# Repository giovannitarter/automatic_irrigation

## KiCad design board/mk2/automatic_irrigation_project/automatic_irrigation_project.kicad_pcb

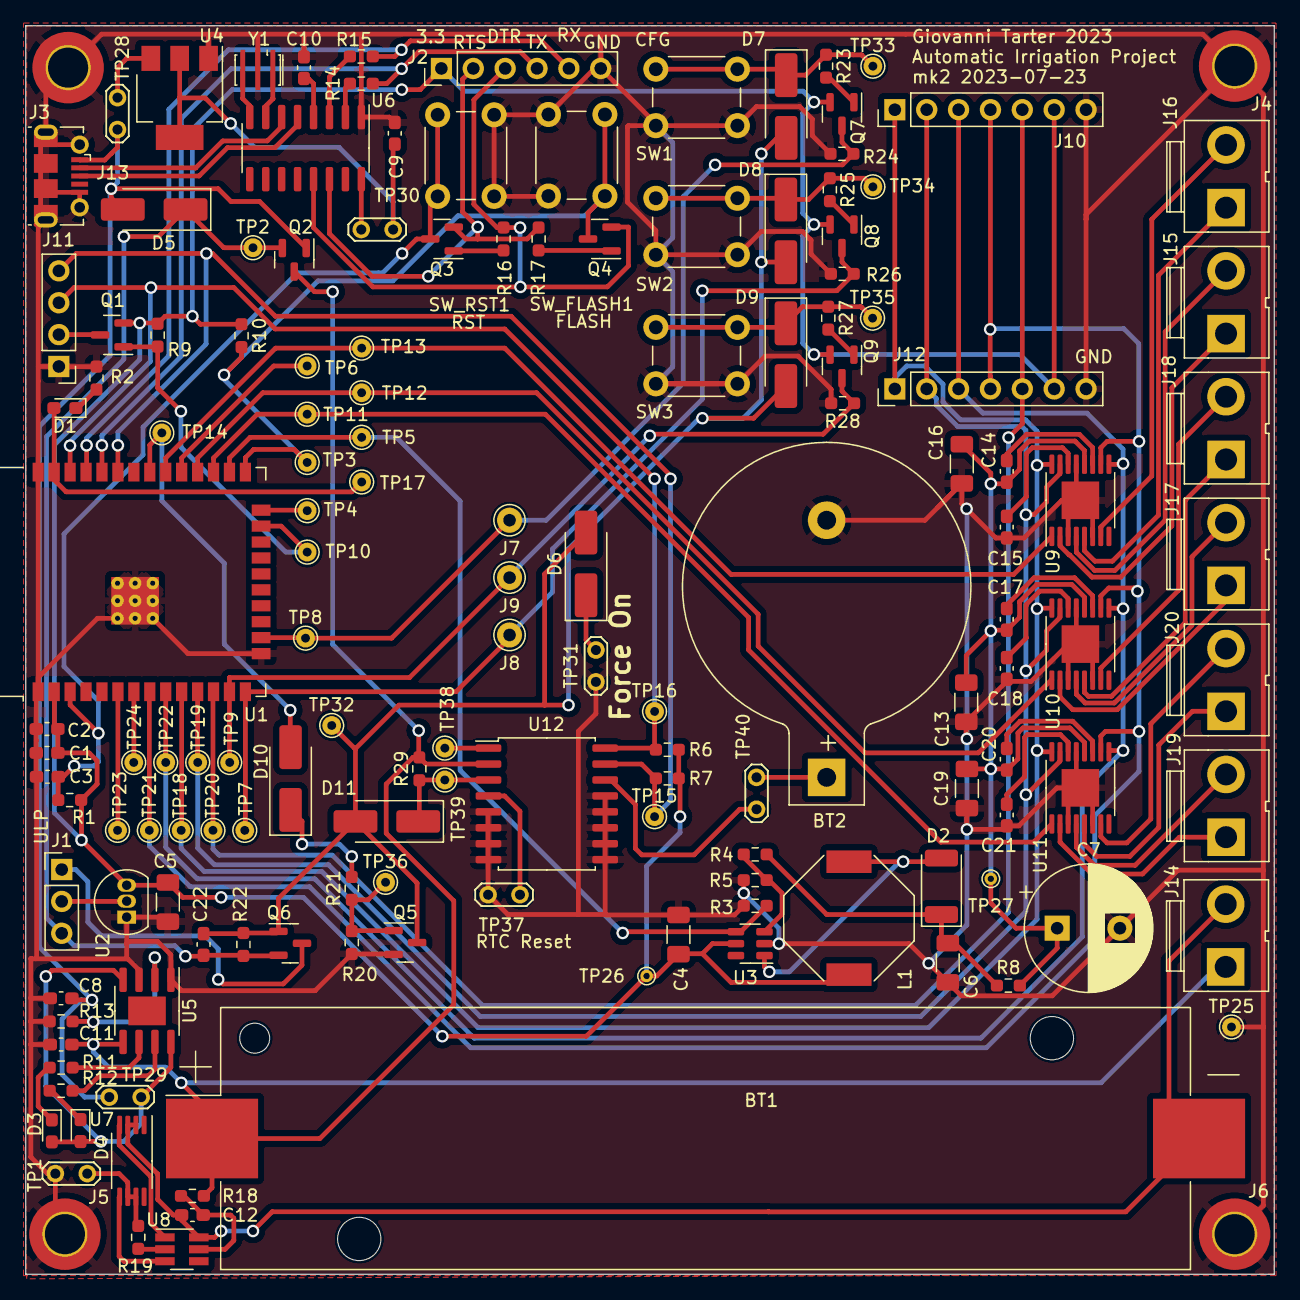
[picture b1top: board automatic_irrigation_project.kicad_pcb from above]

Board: 2 copper layers, 99.5 x 99.5 mm, 152 parts (0 on the bottom side), 97 nets.

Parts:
BT1: Battery; BatteryHolder_Keystone_1042_1x18650
BT2: Battery_Cell; BatteryHolder_Keystone_103_1x20mm
C1, C3, C9, C11: 10uF; C_0603_1608Metric_Pad1.08x0.95mm_HandSolder
C2, C8, C10, C14, C17, C20: 0.1uF; C_0603_1608Metric_Pad1.08x0.95mm_HandSolder
C4, C6: 22uF; C_1206_3216Metric_Pad1.33x1.80mm_HandSolder
C5: 100uF; C_1206_3216Metric_Pad1.33x1.80mm_HandSolder
C7: 1000uF; CP_Radial_D10.0mm_P5.00mm
C12: 100nF; C_0603_1608Metric_Pad1.08x0.95mm_HandSolder
C13, C16, C19: 10uF; C_1206_3216Metric_Pad1.33x1.80mm_HandSolder
C15, C18, C21: 2.2uF; C_0603_1608Metric_Pad1.08x0.95mm_HandSolder
C22: 10n; C_0603_1608Metric_Pad1.08x0.95mm_HandSolder
D1: LED; LED_0603_1608Metric_Pad1.05x0.95mm_HandSolder
D2: 1SS355VM; D_2010_5025Metric
D3: LED G; LED_0603_1608Metric_Pad1.05x0.95mm_HandSolder
D4: LED R; LED_0603_1608Metric_Pad1.05x0.95mm_HandSolder
D5: SS14; D_SMA_Handsoldering
D6, D7, D8, D9, D10, D11: 1N5817; D_SMA_Handsoldering
J1: Conn_01x03_Pin; PinHeader_1x03_P2.54mm_Vertical
J2: Conn_01x06_Pin; PinHeader_1x06_P2.54mm_Vertical
J3, J4, J5, J6: Conn_01x01_Pin; MountingHole_3.2mm_M3_ISO7380_Pad_TopBottom
J7, J8, J9: Conn_01x01_Pin; Pin_D1.0mm_L10.0mm
J10, J12: Conn_01x07_Pin; PinHeader_1x07_P2.54mm_Vertical
J11: Conn_01x04_Pin; PinHeader_1x04_P2.54mm_Vertical
J13: USB_B_Micro; USB_Micro-B_Molex-105017-0001
J14, J15, J16, J17, J18, J19, J20: Conn_01x02; Terminal_5mm
L1: 22uH; L_Bourns-SRU1028_10.0x10.0mm
Q1, Q2, Q6: AO3401A; SOT-23
Q3, Q4, Q5: BC817; SOT-23
Q7, Q8, Q9: BC807; SOT-23
R1, R3, R6, R7, R10, R20, R22, R29: 100K; R_0603_1608Metric_Pad0.98x0.95mm_HandSolder
R2: 330; R_0603_1608Metric_Pad0.98x0.95mm_HandSolder
R4: 180K; R_0603_1608Metric_Pad0.98x0.95mm_HandSolder
R5, R9, R16, R17, R21, R23, R24, R25, R26, R27, R28: 10K; R_0603_1608Metric_Pad0.98x0.95mm_HandSolder
R8, R18: 100 Ohm; R_0603_1608Metric_Pad0.98x0.95mm_HandSolder
R11, R12, R13: 1K; R_0603_1608Metric_Pad0.98x0.95mm_HandSolder
R14, R15: 220; R_0603_1608Metric_Pad0.98x0.95mm_HandSolder
R19: 1k; R_0603_1608Metric_Pad0.98x0.95mm_HandSolder
SW1, SW2, SW3: SW_Push; SW_PUSH_6mm_H4.3mm
SW_FLASH1: SW_Push; SW_PUSH_6mm_H4.3mm
SW_RST1: SW_Push; SW_PUSH_6mm_H4.3mm
TP1, TP28, TP29, TP30, TP31: TestPoint_2Pole; TestPoint_2Pads_Pitch2.54mm_Drill0.8mm
TP2, TP3, TP4, TP5, TP6, TP7, TP8, TP9, TP10, TP11, TP12, TP13, TP14, TP15, TP16, TP17, TP18, TP19, TP20, TP21, TP22, TP23, TP24, TP25, TP32, TP33, TP34, TP35, TP36, TP38, TP39: TestPoint_Probe; TestPoint_THTPad_D1.5mm_Drill0.7mm
TP26, TP27: TestPoint; TestPoint_THTPad_D1.0mm_Drill0.5mm
TP37: RTC Reset; TestPoint_2Pads_Pitch2.54mm_Drill0.8mm
TP40: Bat Exclusion; TestPoint_2Pads_Pitch2.54mm_Drill0.8mm
U1: ESP32-WROOM-32D
U2: HT7333; TO-92L_Inline
U3: MT3608; SOT-23-6
U4: AMS1117-3.3; SOT-223-3_TabPin2
U5: TP4056; SOIC-8-1EP_3.9x4.9mm_P1.27mm_EP2.29x3mm
U6: CH340G; SOIC-16_3.9x9.9mm_P1.27mm
U7: FS8205A; TSSOP-8_4.4x3mm_P0.65mm
U8: DW01; SOT-23-6_Handsoldering
U9, U10, U11: DRV8833PW; HTSSOP-16-1EP_4.4x5mm_P0.65mm_EP3x3mm
U12: DS3231M; SOIC-16W_7.5x10.3mm_P1.27mm
Y1: Resonator; Resonator_SMD_Murata_CSTxExxV-3Pin_3.0x1.1mm_HandSoldering

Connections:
+3.3V: C1.1, C2.1, C4.1, C5.1, J2.1, J10.6, J12.6, L1.1, Q1.2 (S), Q7.2 (E), Q8.2 (E), Q9.2 (E), R1.2, R6.1, R7.1, R9.2, R10.1, TP26.1, U1.2 (VDD), U2.3 (OUT), U3.5 (IN)
+10V: C7.1, C13.1, C14.1, C16.1, C17.1, C19.1, C20.1, R8.2, TP27.1, U9.12 (VM), U10.12 (VM), U11.12 (VM)
+BATT: BT1.1 (+), C11.1, J14.1, Q2.3 (D), R18.2, R29.2, U5.5 (BAT), U12.2 (VCC)
/AIN1: J10.1, J12.1, TP18.1, U1.10 (IO25), U9.16 (AIN1), U10.16 (AIN1), U11.16 (AIN1)
/AIN2: J10.2, J12.2, TP19.1, U1.11 (IO26), U9.15 (AIN2), U10.15 (AIN2), U11.15 (AIN2)
/AUX: J10.5, J12.5, TP20.1, U1.12 (IO27)
/BIN1: J10.3, J12.3, TP22.1, U1.9 (IO33), U9.9 (BIN1), U10.9 (BIN1), U11.9 (BIN1)
/BIN2: J10.4, J12.4, TP21.1, U1.8 (IO32), U9.10 (BIN2), U10.10 (BIN2), U11.10 (BIN2)
/DISP_VCC: Q1.1 (G), R9.1, TP10.1, U1.23 (IO15)
/H_BRIDGE_EN1: TP13.1, U1.30 (IO18), U9.1 (nSLEEP)
/H_BRIDGE_EN2: TP12.1, U1.28 (IO17), U10.1 (nSLEEP)
/H_BRIDGE_EN3: TP11.1, U1.27 (IO16), U11.1 (nSLEEP)
/LATCH: D10.2 (A), TP14.1, U1.31 (IO19)
/RTC_INT: D11.1 (K), R29.1, TP39.1, U12.3 (~INT/SQW)
/SCL: J11.3, R6.2, TP16.1, U1.36 (IO22), U12.16 (SCL)
/SDA: J11.4, R7.2, TP15.1, U1.33 (IO21), U12.15 (SDA)
/STEP_UP_EN: R3.1, TP5.1, U1.26 (IO4), U3.4 (EN)
/SW1: J7.1, Q7.3 (C), R24.1, TP8.1, U1.16 (IO13)
/SW2: J8.1, Q8.3 (C), R26.1, TP7.1, U1.14 (IO12)
/SW3: J9.1, Q9.3 (C), R28.1, TP9.1, U1.13 (IO14)
/battery/BAT-: R19.2, TP1.2, U7.6 (S2), U7.7 (S2)
/power_latch/Vin: C22.1, D5.1 (K), J1.3, Q2.2 (S), Q6.2 (S), R22.2, TP2.1
/power_latch/Vout: J1.1, Q6.3 (D)
DTR: J2.3, Q4.2 (E), R16.1, U6.13 (~DTR)
EN: C3.1, Q3.3 (C), R1.1, SW_RST1.2, U1.3 (EN)
GND: BT2.2 (-), C1.2, C2.2, C3.2, C4.2, C5.2, C6.2, C7.2, C8.2, C9.2, C10.2, C11.2, C13.2, C15.2, C16.2, C18.2, C19.2, C21.2, J2.6, J3.1, J4.1, J5.1, J6.1, J10.7, J11.1, J12.7, J13.5 (GND), J13.6 (Shield), Q5.2 (E), R2.2, R3.2, R5.2, R13.1, R20.2, R24.2, R26.2, R28.2, SW1.1, SW2.1, SW3.1, SW_FLASH1.1, SW_RST1.1, TP1.1, TP25.1, TP31.1, TP37.1, U1.1 (GND), U1.15 (GND), U1.38 (GND), U1.39 (GND), U2.1 (GND), U3.2 (GND), U4.1 (GND), U5.1 (TEMP), U5.3 (GND), U6.1 (GND), U9.3 (AISEN), U9.6 (BISEN), U9.13 (GND), U9.17 (ThermalPad), U10.3 (AISEN), U10.6 (BISEN), U10.13 (GND), U10.17 (ThermalPad), U11.3 (AISEN), U11.6 (BISEN), U11.13 (GND), U11.17 (ThermalPad), U12.5 (GND), U12.6 (GND), U12.7 (GND), U12.8 (GND), U12.9 (GND), U12.10 (GND), U12.11 (GND), U12.12 (GND), U12.13 (GND), Y1.2
IO0: Q4.3 (C), R10.2, SW_FLASH1.2, TP3.1, U1.25 (IO0)
unnamed: BT1.2 (-), C12.2, J14.2, U7.2 (S1), U7.3 (S1), U8.6 (GND)
unnamed: BT2.1 (+), TP40.1
unnamed: D1.2 (A), TP17.1, U1.37 (IO23)
unnamed: D1.1 (K), R2.1
unnamed: D2.2 (A), L1.2, U3.1 (SW)
unnamed: C6.1, D2.1 (K), R4.1, R8.1
unnamed: D3.2 (A), D4.2 (A), TP29.1, U5.4 (VCC), U5.8 (CE)
unnamed: D3.1 (K), R11.2
unnamed: D4.1 (K), R12.2
unnamed: D6.1 (K), TP31.2
unnamed: D7.1 (K), R23.1, SW1.2, TP33.1
unnamed: D8.1 (K), R25.1, SW2.2, TP34.1
unnamed: D9.1 (K), R27.1, SW3.2, TP35.1
unnamed: D10.1 (K), R21.2
unnamed: C22.2, D6.2 (A), D7.2 (A), D8.2 (A), D9.2 (A), D11.2 (A), Q5.3 (C), Q6.1 (G), R22.1, TP32.1
unnamed: J1.2, U2.2 (IN)
unnamed: J11.2, Q1.3 (D)
unnamed: J13.3 (D+), U6.5 (UD+)
unnamed: J13.2 (D-), U6.6 (UD-)
unnamed: J15.1, U9.2 (AOUT1)
unnamed: J15.2, U9.4 (AOUT2)
unnamed: J16.1, U9.5 (BOUT2)
unnamed: J16.2, U9.7 (BOUT1)
unnamed: J17.1, U10.2 (AOUT1)
unnamed: J17.2, U10.4 (AOUT2)
unnamed: J18.1, U10.5 (BOUT2)
unnamed: J18.2, U10.7 (BOUT1)
unnamed: J19.1, U11.2 (AOUT1)
unnamed: J19.2, U11.4 (AOUT2)
unnamed: J20.1, U11.5 (BOUT2)
unnamed: J20.2, U11.7 (BOUT1)
unnamed: Q3.1 (B), R16.2
unnamed: Q4.1 (B), R17.2
unnamed: Q5.1 (B), R20.1, R21.1, TP36.1
unnamed: Q7.1 (B), R23.2
unnamed: Q8.1 (B), R25.2
unnamed: Q9.1 (B), R27.2
unnamed: TP4.1, U1.24 (IO2)
unnamed: TP6.1, U1.29 (IO5)
unnamed: TP23.1, U1.6 (IO34)
unnamed: TP24.1, U1.7 (IO35)
unnamed: R4.2, R5.1, U3.3 (FB)
unnamed: TP28.2, U4.3 (VI)
unnamed: C9.1, TP30.2, U4.2 (VO)
unnamed: R13.2, U5.2 (PROG)
unnamed: R12.1, U5.7 (~CHRG)
unnamed: R11.1, U5.6 (~STDBY)
unnamed: R15.1, U6.3 (RXD)
unnamed: R14.1, U6.2 (TXD)
unnamed: C10.1, U6.4 (V3)
unnamed: TP30.1, U6.16 (VCC)
unnamed: U6.7 (XI), Y1.1
unnamed: U6.8 (XO), Y1.3
unnamed: U7.4 (G1), U8.1 (OD)
unnamed: U7.5 (G2), U8.3 (OC)
unnamed: R19.1, U8.2 (CS)
unnamed: C12.1, R18.1, U8.5 (VCC)
unnamed: C14.2, U9.11 (VCP)
unnamed: C15.1, U9.14 (VINT)
unnamed: C17.2, U10.11 (VCP)
unnamed: C18.1, U10.14 (VINT)
unnamed: C20.2, U11.11 (VCP)
unnamed: C21.1, U11.14 (VINT)
unnamed: TP38.1, U12.1 (32KHZ)
unnamed: TP40.2, U12.14 (VBAT)
unnamed: TP37.2, U12.4 (~RST)
RTS: J2.2, Q3.2 (E), R17.1, U6.14 (~RTS)
RX: J2.5, R15.2, U1.35 (TXD0/IO1)
TX: J2.4, R14.2, U1.34 (RXD0/IO3)
VUSB: C8.1, D5.2 (A), J13.1 (VBUS), Q2.1 (G), TP28.1, TP29.2

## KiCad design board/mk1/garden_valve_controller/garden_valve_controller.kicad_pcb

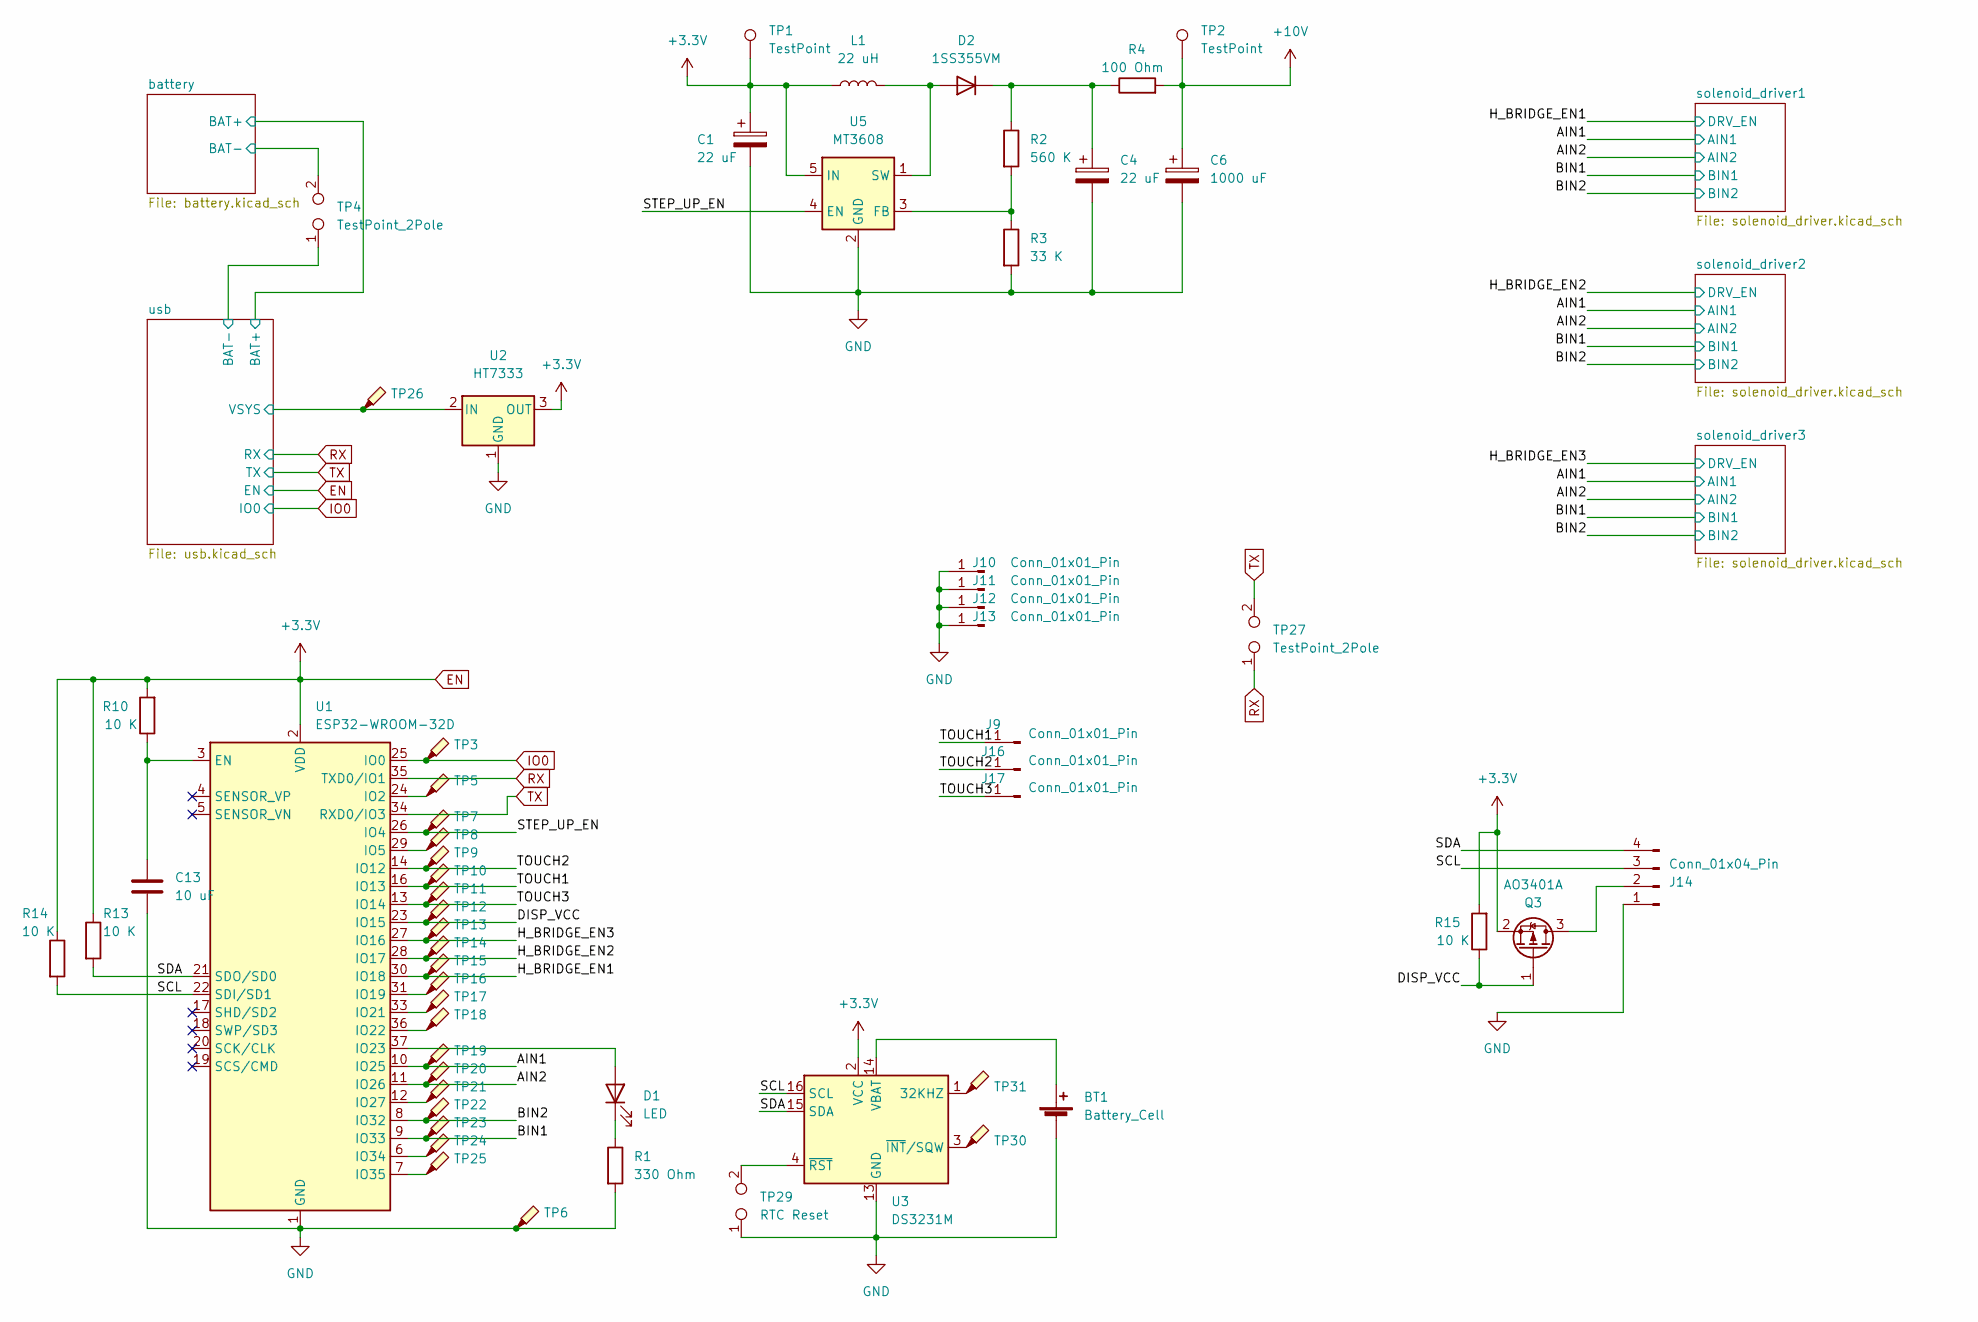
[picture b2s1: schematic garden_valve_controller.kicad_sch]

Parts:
BT1: Battery_Cell; BatteryHolder_Keystone_103_1x20mm
C1, C4: 22 uF; C_1206_3216Metric_Pad1.33x1.80mm_HandSolder
C6: 1000 uF; CP_Radial_D10.0mm_P5.00mm
C13: 10 uF; C_0603_1608Metric_Pad1.08x0.95mm_HandSolder
D1: LED; LED_D3.0mm_Clear
D2: 1SS355VM; D_2010_5025Metric
J9, J16, J17: Conn_01x01_Pin; Pin_D1.0mm_L10.0mm
J10, J11, J12, J13: Conn_01x01_Pin; MountingHole_3.2mm_M3_ISO7380_Pad_TopBottom
J14: Conn_01x04_Pin; PinHeader_1x04_P2.54mm_Vertical
L1: 22 uH; L_Bourns-SRU1028_10.0x10.0mm
Q3: AO3401A; SOT-23
R1: 330 Ohm; R_0603_1608Metric_Pad0.98x0.95mm_HandSolder
R2: 560 K; R_0603_1608Metric_Pad0.98x0.95mm_HandSolder
R3: 33 K; R_0603_1608Metric_Pad0.98x0.95mm_HandSolder
R4: 100 Ohm; R_0603_1608Metric_Pad0.98x0.95mm_HandSolder
R10, R13, R14, R15: 10 K; R_0603_1608Metric_Pad0.98x0.95mm_HandSolder
TP1, TP2: TestPoint; TestPoint_THTPad_D1.0mm_Drill0.5mm
TP3, TP5, TP6, TP7, TP8, TP9, TP10, TP11, TP12, TP13, TP14, TP15, TP16, TP17, TP18, TP19, TP20, TP21, TP22, TP23, TP24, TP25, TP26, TP30, TP31: TestPoint_Probe; TestPoint_THTPad_D1.0mm_Drill0.5mm
TP4, TP27: TestPoint_2Pole; TestPoint_2Pads_Pitch2.54mm_Drill0.8mm
TP29: RTC Reset; TestPoint_2Pads_Pitch2.54mm_Drill0.8mm
U1: ESP32-WROOM-32D
U2: HT7333; TO-92L_Inline
U3: DS3231M; SOIC-16W_7.5x10.3mm_P1.27mm
U5: MT3608; SOT-23-6

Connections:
+10V: C6.1, R4.2, TP2.1; also elsewhere on the board
/AIN1: TP19.1, U1.10 (IO25); also elsewhere on the board
/AIN2: TP20.1, U1.11 (IO26); also elsewhere on the board
/BIN1: TP23.1, U1.9 (IO33); also elsewhere on the board
/BIN2: TP22.1, U1.8 (IO32); also elsewhere on the board
/H_BRIDGE_EN1: TP15.1, U1.30 (IO18); also elsewhere on the board
/H_BRIDGE_EN2: TP14.1, U1.28 (IO17); also elsewhere on the board
/H_BRIDGE_EN3: TP13.1, U1.27 (IO16); also elsewhere on the board
/SCL: J14.3, R14.2, U1.22 (SDI/SD1), U3.16 (SCL)
/SDA: J14.4, R13.2, U1.21 (SDO/SD0), U3.15 (SDA)
/STEP_UP_EN: TP7.1, U1.26 (IO4), U5.4 (EN)
/TOUCH1: J9.1, TP10.1, U1.16 (IO13)
/TOUCH2: J16.1, TP9.1, U1.14 (IO12)
/TOUCH3: J17.1, TP11.1, U1.13 (IO14)
/battery/BAT-: TP4.2; also elsewhere on the board
GND: BT1.2 (-), C1.2, C4.2, C6.2, C13.2, J10.1, J11.1, J12.1, J13.1, J14.1, R1.2, R3.2, TP4.1, TP6.1, TP29.1, U1.1 (GND), U1.15 (GND), U1.38 (GND), U1.39 (GND), U2.1 (GND), U3.5 (GND), U3.6 (GND), U3.7 (GND), U3.8 (GND), U3.9 (GND), U3.10 (GND), U3.11 (GND), U3.12 (GND), U3.13 (GND), U5.2 (GND); also elsewhere on the board
IO0: TP3.1, U1.25 (IO0); also elsewhere on the board
unnamed: BT1.1 (+), U3.14 (VBAT)
unnamed: D1.2 (A), U1.37 (IO23)
unnamed: D1.1 (K), R1.1
unnamed: D2.2 (A), L1.2, U5.1 (SW)
unnamed: C4.1, D2.1 (K), R2.1, R4.1
unnamed: C13.1, R10.1, U1.3 (EN)
unnamed: TP5.1, U1.24 (IO2)
unnamed: TP8.1, U1.29 (IO5)
unnamed: TP16.1, U1.31 (IO19)
unnamed: TP17.1, U1.33 (IO21)
unnamed: TP18.1, U1.36 (IO22)
unnamed: TP21.1, U1.12 (IO27)
unnamed: TP24.1, U1.6 (IO34)
unnamed: TP25.1, U1.7 (IO35)
unnamed: TP31.1, U3.1 (32KHZ)
unnamed: TP30.1, U3.3 (~INT/SQW)
unnamed: TP29.2, U3.4 (~RST)
unnamed: R2.2, R3.1, U5.3 (FB)
RX: TP27.1, U1.35 (TXD0/IO1); also elsewhere on the board
TX: TP27.2, U1.34 (RXD0/IO3); also elsewhere on the board

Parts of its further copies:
Q4: AO3401A; SOT-23

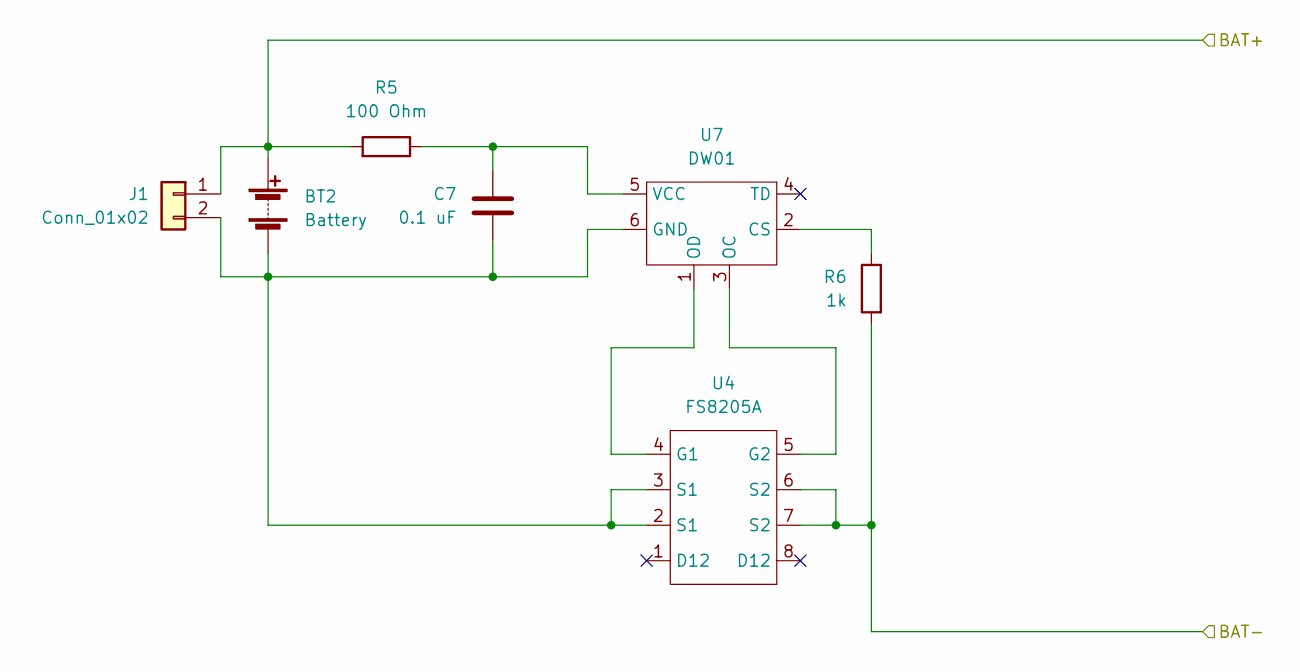
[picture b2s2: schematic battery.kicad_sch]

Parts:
BT2: Battery; BatteryHolder_MPD_BH-18650-PC2
C7: 0.1 uF; C_0603_1608Metric_Pad1.08x0.95mm_HandSolder
J1: Conn_01x02; Terminal_5mm
R5: 100 Ohm; R_0603_1608Metric_Pad0.98x0.95mm_HandSolder
R6: 1k; R_0603_1608Metric_Pad0.98x0.95mm_HandSolder
U4: FS8205A; TSSOP-8_4.4x3mm_P0.65mm
U7: DW01; SOT-23-6_Handsoldering

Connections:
/battery/BAT-: R6.2, U4.6 (S2), U4.7 (S2); also elsewhere on the board
unnamed: BT2.2 (-), C7.2, J1.2, U4.2 (S1), U4.3 (S1), U7.6 (GND)
unnamed: U4.4 (G1), U7.1 (OD)
unnamed: U4.5 (G2), U7.3 (OC)
unnamed: R6.1, U7.2 (CS)
unnamed: C7.1, R5.1, U7.5 (VCC)

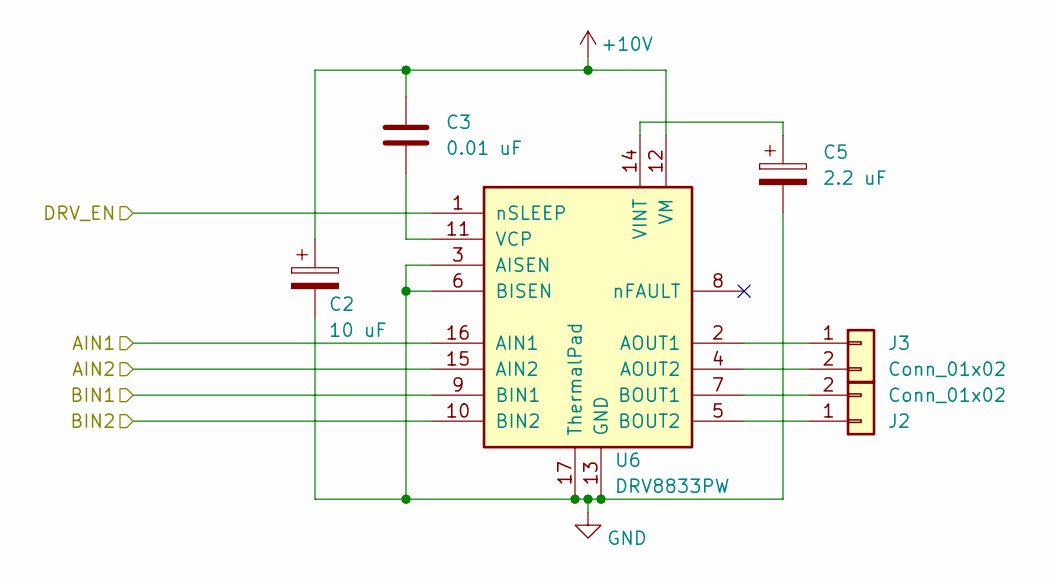
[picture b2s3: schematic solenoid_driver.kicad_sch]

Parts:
C2: 10 uF; C_1206_3216Metric_Pad1.33x1.80mm_HandSolder
C3: 0.01 uF; C_0603_1608Metric_Pad1.08x0.95mm_HandSolder
C5: 2.2 uF; C_0603_1608Metric_Pad1.08x0.95mm_HandSolder
J2, J3: Conn_01x02; Terminal_5mm
U6: DRV8833PW; HTSSOP-16-1EP_4.4x5mm_P0.65mm_EP3x3mm

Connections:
+10V: C2.1, C3.1, U6.12 (VM); also elsewhere on the board
/AIN1: U6.16 (AIN1); also elsewhere on the board
/AIN2: U6.15 (AIN2); also elsewhere on the board
/BIN1: U6.9 (BIN1); also elsewhere on the board
/BIN2: U6.10 (BIN2); also elsewhere on the board
/H_BRIDGE_EN1: U6.1 (nSLEEP); also elsewhere on the board
GND: C2.2, C5.2, U6.3 (AISEN), U6.6 (BISEN), U6.13 (GND), U6.17 (ThermalPad); also elsewhere on the board
unnamed: J2.1, U6.5 (BOUT2)
unnamed: J2.2, U6.7 (BOUT1)
unnamed: J3.1, U6.2 (AOUT1)
unnamed: J3.2, U6.4 (AOUT2)
unnamed: C3.2, U6.11 (VCP)
unnamed: C5.1, U6.14 (VINT)

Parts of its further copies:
C9, C16: 10 uF; C_1206_3216Metric_Pad1.33x1.80mm_HandSolder
C10, C17: 0.01 uF; C_0603_1608Metric_Pad1.08x0.95mm_HandSolder
C15, C18: 2.2 uF; C_0603_1608Metric_Pad1.08x0.95mm_HandSolder
J5, J6, J7, J8: Conn_01x02; Terminal_5mm
U11, U12: DRV8833PW; HTSSOP-16-1EP_4.4x5mm_P0.65mm_EP3x3mm

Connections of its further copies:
+10V: C9.1, C10.1, C16.1, C17.1, U11.12 (VM), U12.12 (VM); also elsewhere on the board
/AIN1: U11.16 (AIN1), U12.16 (AIN1); also elsewhere on the board
/AIN2: U11.15 (AIN2), U12.15 (AIN2); also elsewhere on the board
/BIN1: U11.9 (BIN1), U12.9 (BIN1); also elsewhere on the board
/BIN2: U11.10 (BIN2), U12.10 (BIN2); also elsewhere on the board
/H_BRIDGE_EN2: U11.1 (nSLEEP); also elsewhere on the board
/H_BRIDGE_EN3: U12.1 (nSLEEP); also elsewhere on the board
GND: C9.2, C15.2, C16.2, C18.2, U11.3 (AISEN), U11.6 (BISEN), U11.13 (GND), U11.17 (ThermalPad), U12.3 (AISEN), U12.6 (BISEN), U12.13 (GND), U12.17 (ThermalPad); also elsewhere on the board
unnamed: J5.1, U11.5 (BOUT2)
unnamed: J5.2, U11.7 (BOUT1)
unnamed: J6.1, U11.2 (AOUT1)
unnamed: J6.2, U11.4 (AOUT2)
unnamed: J7.1, U12.5 (BOUT2)
unnamed: J7.2, U12.7 (BOUT1)
unnamed: J8.1, U12.2 (AOUT1)
unnamed: J8.2, U12.4 (AOUT2)
unnamed: C10.2, U11.11 (VCP)
unnamed: C15.1, U11.14 (VINT)
unnamed: C17.2, U12.11 (VCP)
unnamed: C18.1, U12.14 (VINT)

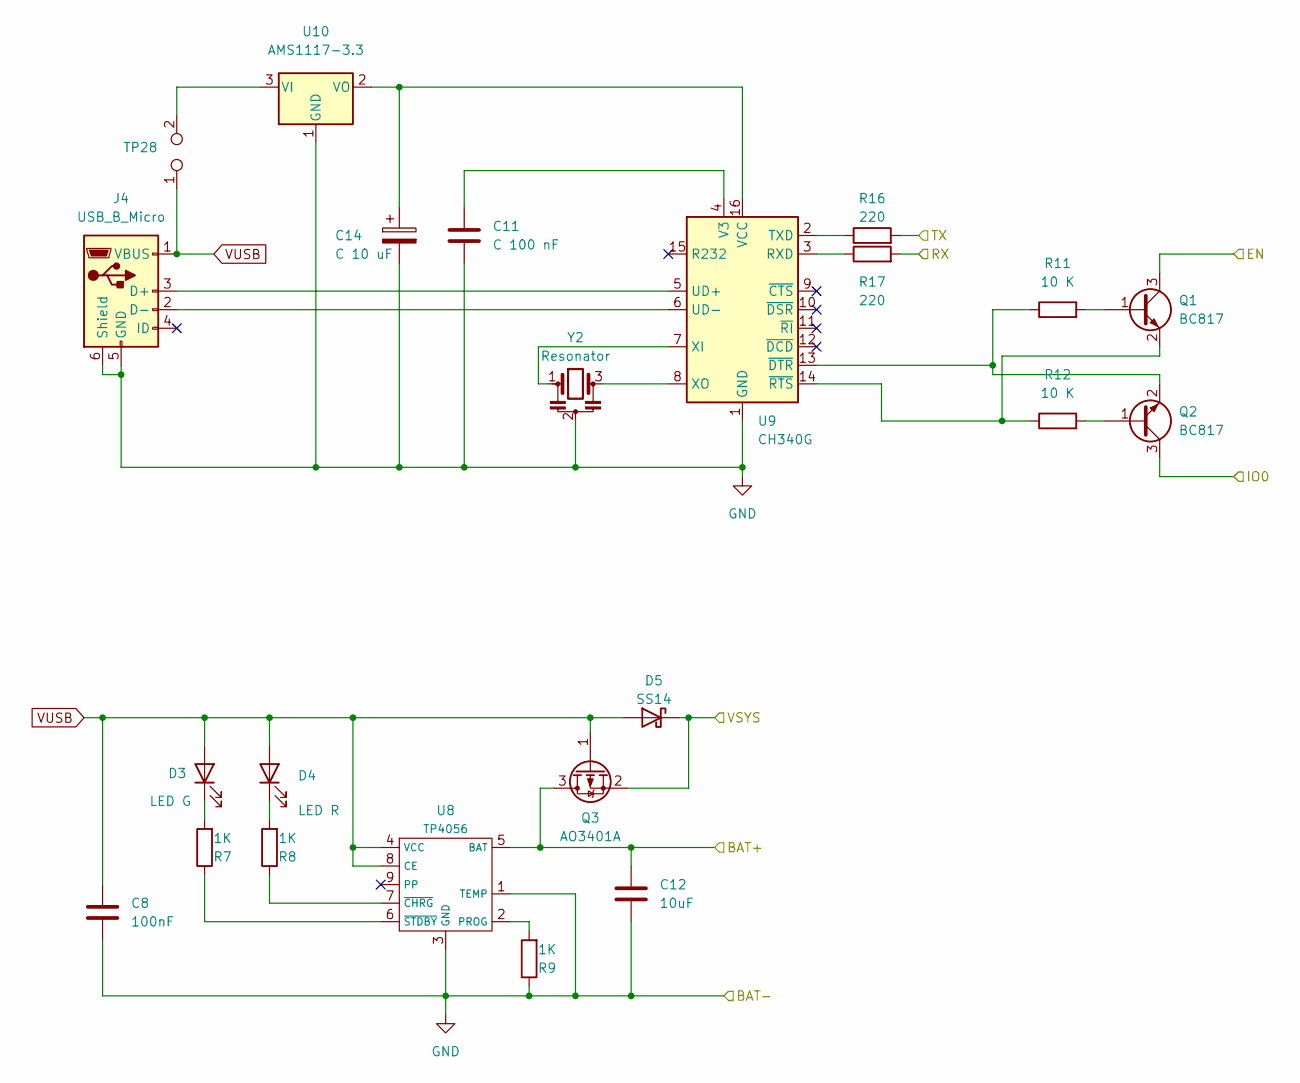
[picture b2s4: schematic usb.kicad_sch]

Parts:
C8: 100nF; C_0603_1608Metric_Pad1.08x0.95mm_HandSolder
C11: C 100 nF; C_0603_1608Metric_Pad1.08x0.95mm_HandSolder
C12: 10uF; C_0603_1608Metric_Pad1.08x0.95mm_HandSolder
C14: C 10 uF; C_0603_1608Metric_Pad1.08x0.95mm_HandSolder
D3: LED G; LED_D3.0mm_Clear
D4: LED R; LED_D3.0mm_Clear
D5: SS14; D_SMA_Handsoldering
J4: USB_B_Micro; USB_Micro-B_Molex-105017-0001
Q1, Q2: BC817; SOT-23
Q3: AO3401A; SOT-23
R7, R8, R9: 1K; R_0603_1608Metric_Pad0.98x0.95mm_HandSolder
R11, R12: 10 K; R_0603_1608Metric_Pad0.98x0.95mm_HandSolder
R16, R17: 220; R_0603_1608Metric_Pad0.98x0.95mm_HandSolder
TP28: TestPoint_2Pole; TestPoint_2Pads_Pitch2.54mm_Drill0.8mm
U8: TP4056; SOIC-8-1EP_3.9x4.9mm_P1.27mm_EP2.29x3mm
U9: CH340G; SOIC-16_3.9x9.9mm_P1.27mm
U10: AMS1117-3.3; SOT-223-3_TabPin2
Y2: Resonator; Resonator_SMD_Murata_CSTxExxV-3Pin_3.0x1.1mm_HandSoldering

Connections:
GND: C8.2, C11.2, C12.2, C14.2, J4.5 (GND), J4.6 (Shield), R9.1, U8.1 (TEMP), U8.3 (GND), U9.1 (GND), U10.1 (GND), Y2.2; also elsewhere on the board
IO0: Q2.3 (C); also elsewhere on the board
unnamed: D3.1 (K), R7.2
unnamed: D4.1 (K), R8.2
unnamed: J4.3 (D+), U9.5 (UD+)
unnamed: J4.2 (D-), U9.6 (UD-)
unnamed: Q1.1 (B), R11.2
unnamed: Q1.2 (E), R12.1, U9.14 (~RTS)
unnamed: Q2.1 (B), R12.2
unnamed: Q2.2 (E), R11.1, U9.13 (~DTR)
unnamed: R9.2, U8.2 (PROG)
unnamed: R8.1, U8.7 (~CHRG)
unnamed: R7.1, U8.6 (~STDBY)
unnamed: R17.1, U9.3 (RXD)
unnamed: R16.1, U9.2 (TXD)
unnamed: C11.1, U9.4 (V3)
unnamed: U9.7 (XI), Y2.1
unnamed: U9.8 (XO), Y2.3
unnamed: TP28.2, U10.3 (VI)
unnamed: C14.1, U9.16 (VCC), U10.2 (VO)
RX: R17.2; also elsewhere on the board
TX: R16.2; also elsewhere on the board

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
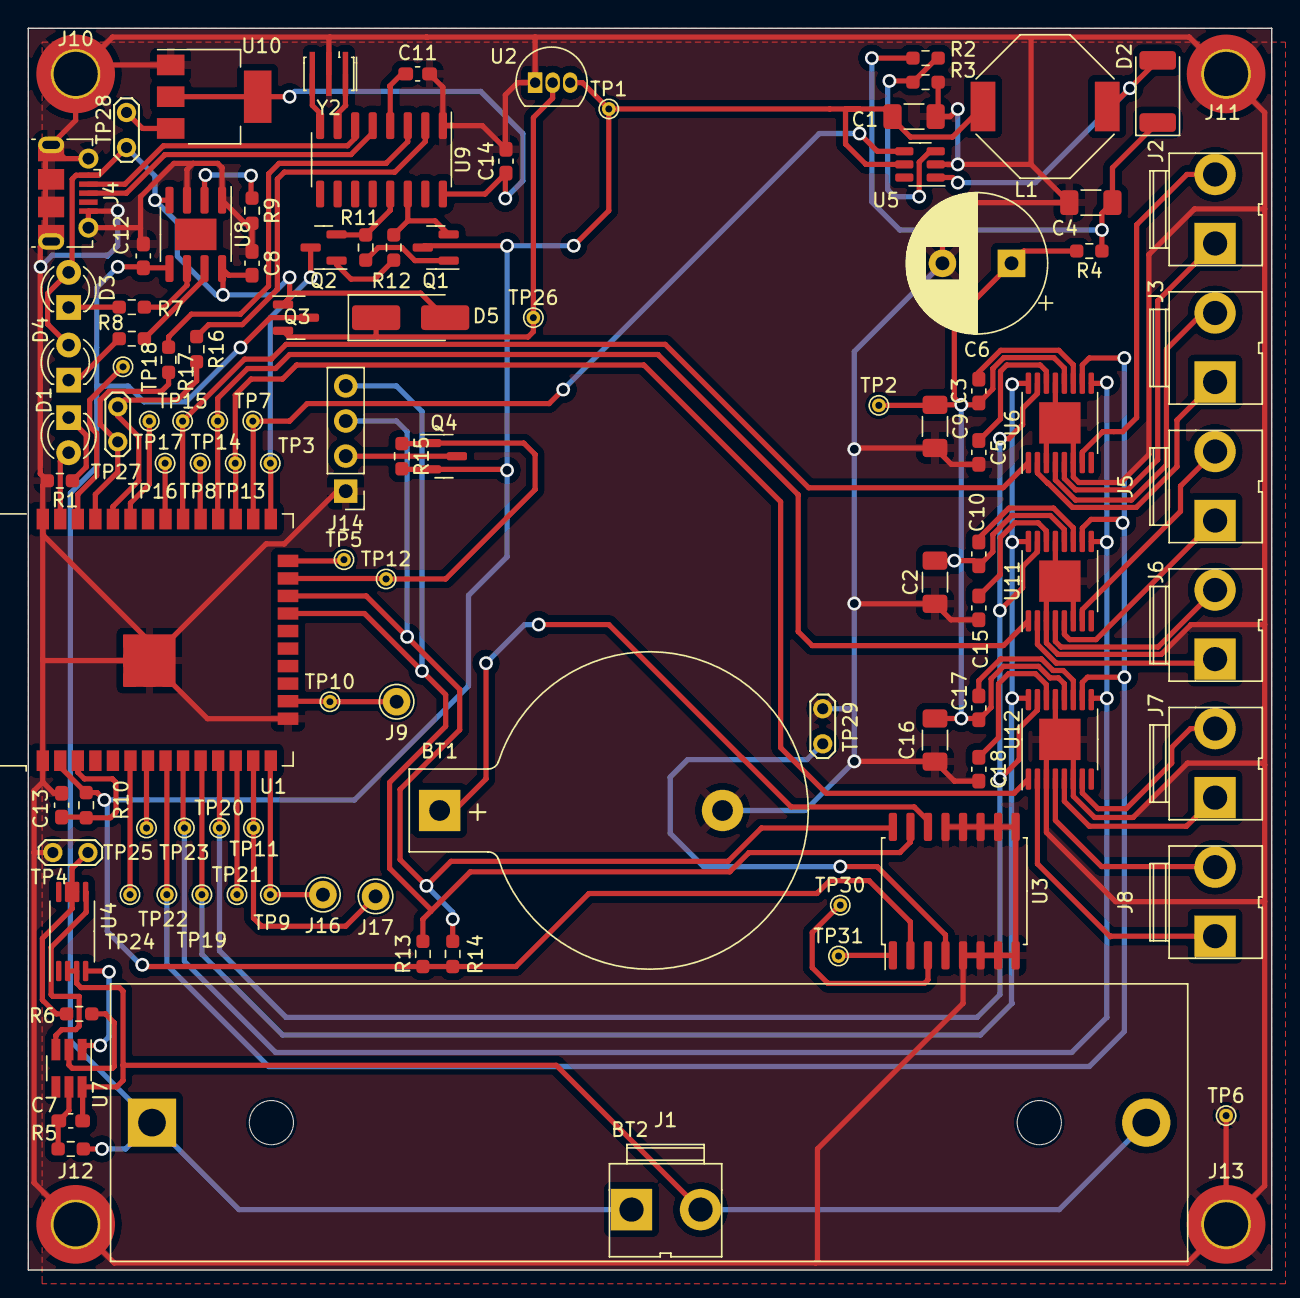
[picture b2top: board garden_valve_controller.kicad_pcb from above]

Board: 2 copper layers, 90.0 x 89.9 mm, 107 parts (0 on the bottom side), 84 nets.

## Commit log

2023-05-14 initial
    - committing board printed on 2023-05-13
2023-06-12 firmware initial
2023-06-18 fixes
2023-06-20 moving src in lib dir
2023-06-21 using esp32 gpio pin facilities
2023-07-01 backup
2023-07-07 modified: compile.sh modified: docker/Dockerfile
2023-07-08 adding alarm
2023-07-23 second printed board (mk2)
2023-07-25 regenerate schematic plots and bom
2023-08-17 new fw, tasks, queues
